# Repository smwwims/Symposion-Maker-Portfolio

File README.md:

# Symposion – Autonomous Service Robot (Maker Portfolio Version)

This repository is a public showcase of my **Symposion** transport robot project, created originally as my final mechatronics graduation project on top of a Festo Robotino platform. The private project repo (in German) also contained invoices and personal data, so this version focuses on the technical artefacts: **application code, mechanical CAD, and PCB design files**. It contains the **current implementation**, not the full incremental history.

## Software Overview

The main control programs for the robot are written in Festo’s proprietary environment **RobotinoView**, which combines Sequential Function Chart (SFC) and Function Block Diagram (FBD) and allows integrating **Python scripts as custom function blocks**. RobotinoView provides blocks for each integrated hardware component, libraries for robotics functions such as odometry, and mathematical operations; the entire **autonomous driving and docking logic** is implemented in this environment.

Python scripts act as intermediaries between the web interface, custom sensors, and the Robotino framework. The following scripts are used as function blocks inside the main RobotinoView program:

- `alarm.py` – triggers sound and light signals in case of an impending collision.
- `encoder.py` – passes encoder measurements to the web interface.
- `readPath.py` – retrieves permanently stored routes from a CSV file.
- `restart.py` – sends a restart signal to Robotino once it has reached the last waypoint.

Because I added custom sensors (ToF distance sensors, IR receiver/transmitter) and outputs (LED strips) that cannot be connected directly to Robotino’s I/O, I integrated an **Arduino Nano as an intermediate controller**.

- `k3_control.ino` runs continuously on the Nano, reading ToF distance values and IR receiver signals and outputting color commands as PWM signals to the LED strips.
- In parallel, `k3_communication.py` runs on Robotino’s Ubuntu-based control unit (started automatically via `startSymposion.sh`). It establishes a USB connection to the Arduino, writes distance measurements into `.txt` files that RobotinoView reads, and forwards color commands from the Flask web interface to the Arduino.

The **web interface** is built with the Flask framework. It can either talk to Robotino hardware via a REST API or write control data into `.txt` files that are consumed by the other software modules.

## Repository Structure

### `Software/`

Contains the Python scripts, Arduino code, and supporting files used alongside RobotinoView. RobotinoView project files themselves are not easily diff‑friendly, but the structure and naming of the Python and Arduino modules mirror the logical modules described in the project documentation (route following, docking, safety, communication).

### `Mechanics/`

Contains the **mechanical design files** for the robot add‑ons I designed. This includes:

- The **linear axis** mounted on top of the Robotino for the height‑adjustable platform.
- The **circular platform table** with carved bottle placements.
- The **internal platform** for additional sensors and electronics.
- Exported formats suitable for viewing (e.g., STEP) and integration into other CAD assemblies.

Vendor parts such as the Robotino base, standard aluminum profiles, and hardware are represented using manufacturer CAD where available.

### `Electronics/`

Contains the **PCB design artefacts** and related documentation for the custom Arduino peripheral interface board (“K3 – Arduino Peripheral IF”). This includes:

- **Schematics**
- **Board Layouts**
- **Bill of Materials (BoM)** with reference designators, descriptions, and supplier part numbers for key components (MOSFETs, connectors, resistors, capacitors, and the PCB itself).

This board interfaces 5 V sensors (ToF, IR receiver), drives LED strips, and communicates with Robotino’s control unit via USB through an Arduino Nano.

## Notes

- This repo is intended as a **readable technical snapshot** of the project, not as a polished, general‑purpose library.
- For a complete system description (mechanics, electronics, software, risk analysis, and operating manual), see the accompanying [project documentation](Symposion_SMW_2023_EN.pdf).

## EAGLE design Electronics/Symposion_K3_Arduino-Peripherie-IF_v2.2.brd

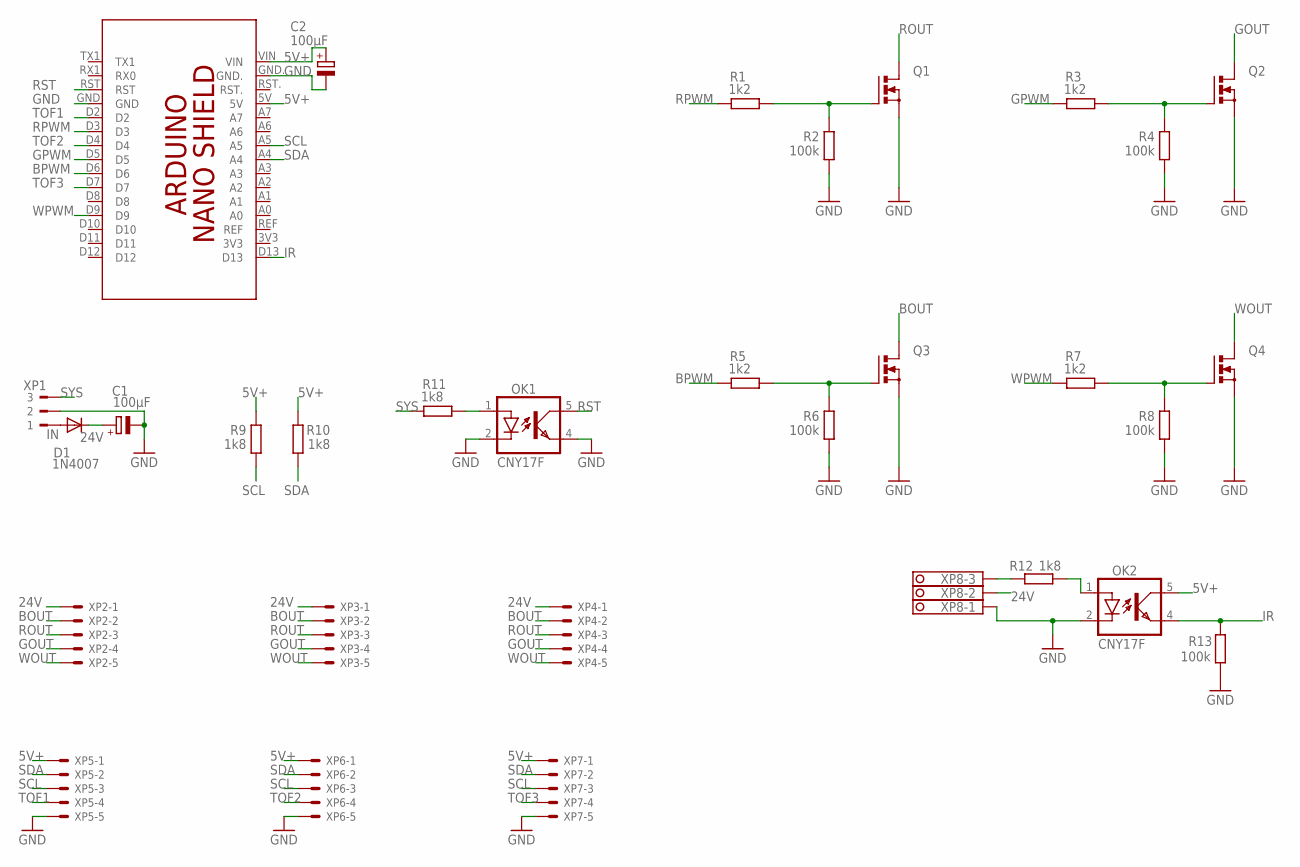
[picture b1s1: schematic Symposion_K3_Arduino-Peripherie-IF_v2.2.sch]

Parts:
C1, C2: 100µF; RCL_E5-6
D1: 1N4007; DIODE_F126-10
OK1, OK2: CNY17F; DIL06
PCB1: 0_WSH_FAVORITES_ARDUINO_NANO
Q1, Q2, Q3, Q4: 0_WSH_FAVORITES_BUZ11BV; 0_WSH_FAVORITES_TO220BV
R1, R3, R5, R7: 1k2; R1206
R2, R4, R6, R8, R13: 100k; R1206
R9, R10, R11, R12: 1k8; R1206
XP1: 180-3
XP2, XP3, XP4, XP5, XP6, XP7: 22-27-2051-05; 6410-05
XP8: 1751251

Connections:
5V+: C2.+, OK2.5 (COL), PCB1.5V, PCB1.VIN, R9.1, R10.1, XP5.1, XP6.1, XP7.1
24V: C1.+, D1.C, XP2.1, XP3.1, XP4.1, XP8.2
BOUT: Q3.D, XP2.2, XP3.2, XP4.2
BPWM: PCB1.D6, R5.2
GND: C1.-, C2.-, OK1.2 (C), OK1.4 (EMIT), OK2.2 (C), PCB1.GND, PCB1.GND., Q1.S, Q2.S, Q3.S, Q4.S, R2.2, R4.2, R6.2, R8.2, R13.2, XP1.2, XP5.5, XP6.5, XP7.5, XP8.1
GOUT: Q2.D, XP2.4, XP3.4, XP4.4
GPWM: PCB1.D5, R3.2
IN: D1.A, XP1.1
IR: OK2.4 (EMIT), PCB1.D13, R13.1
unnamed: Q1.G, R1.1, R2.1
unnamed: OK1.1 (A), R11.1
unnamed: Q2.G, R3.1, R4.1
unnamed: Q3.G, R5.1, R6.1
unnamed: OK2.1 (A), R12.1
unnamed: Q4.G, R7.1, R8.1
unnamed: R12.2, XP8.3
ROUT: Q1.D, XP2.3, XP3.3, XP4.3
RPWM: PCB1.D3, R1.2
RST: OK1.5 (COL), PCB1.RST
SCL: PCB1.A5, R9.2, XP5.3, XP6.3, XP7.3
SDA: PCB1.A4, R10.2, XP5.2, XP6.2, XP7.2
SYS: R11.2, XP1.3
TOF1: PCB1.D2, XP5.4
TOF2: PCB1.D4, XP6.4
TOF3: PCB1.D7, XP7.4
WOUT: Q4.D, XP2.5, XP3.5, XP4.5
WPWM: PCB1.D9, R7.2

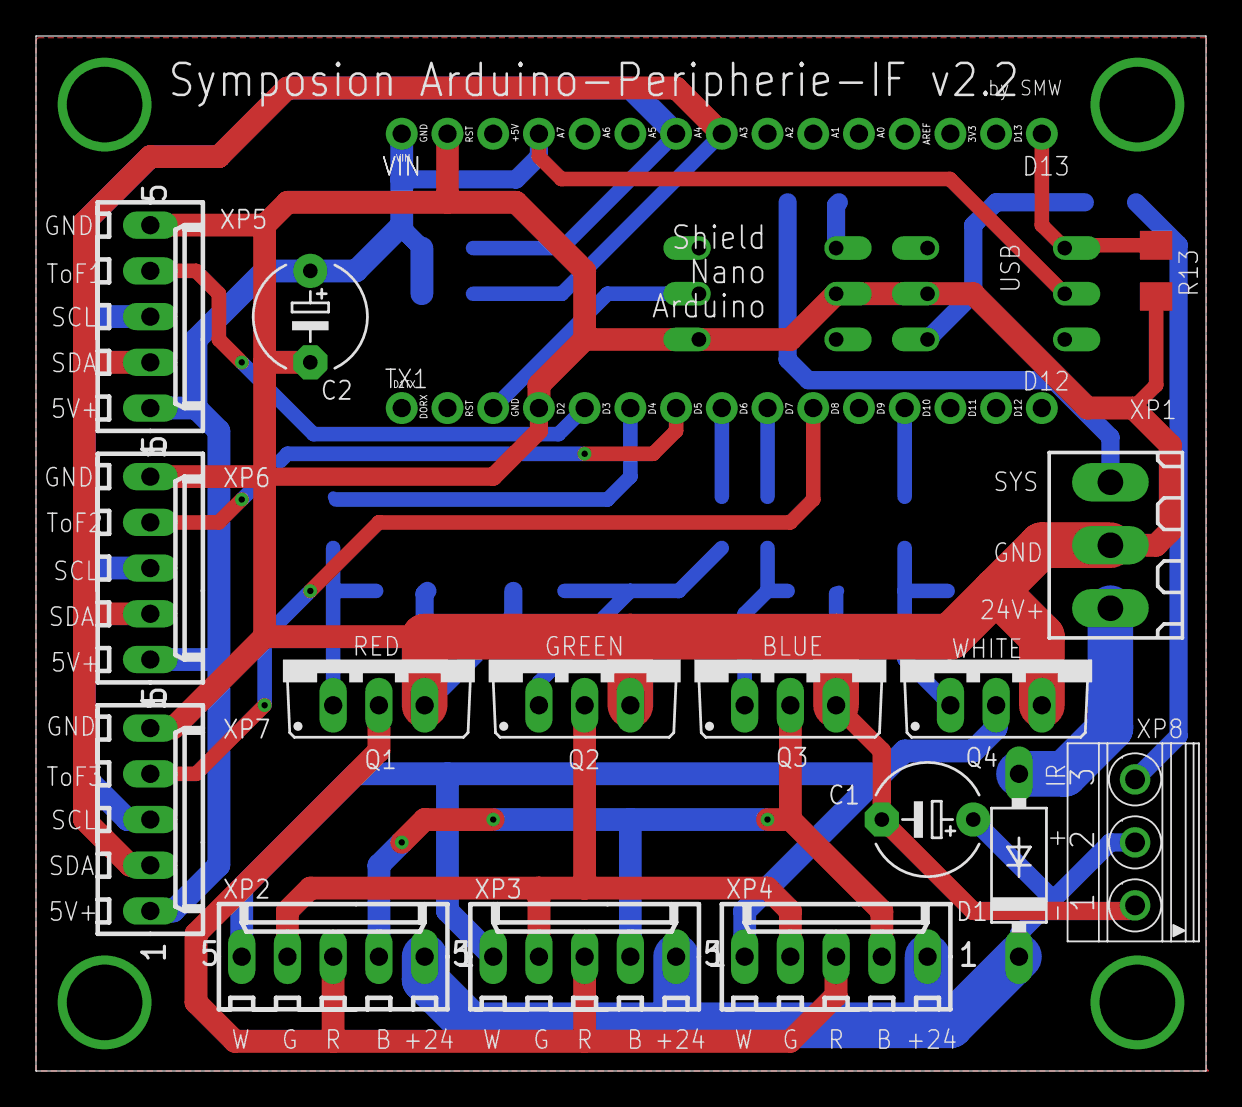
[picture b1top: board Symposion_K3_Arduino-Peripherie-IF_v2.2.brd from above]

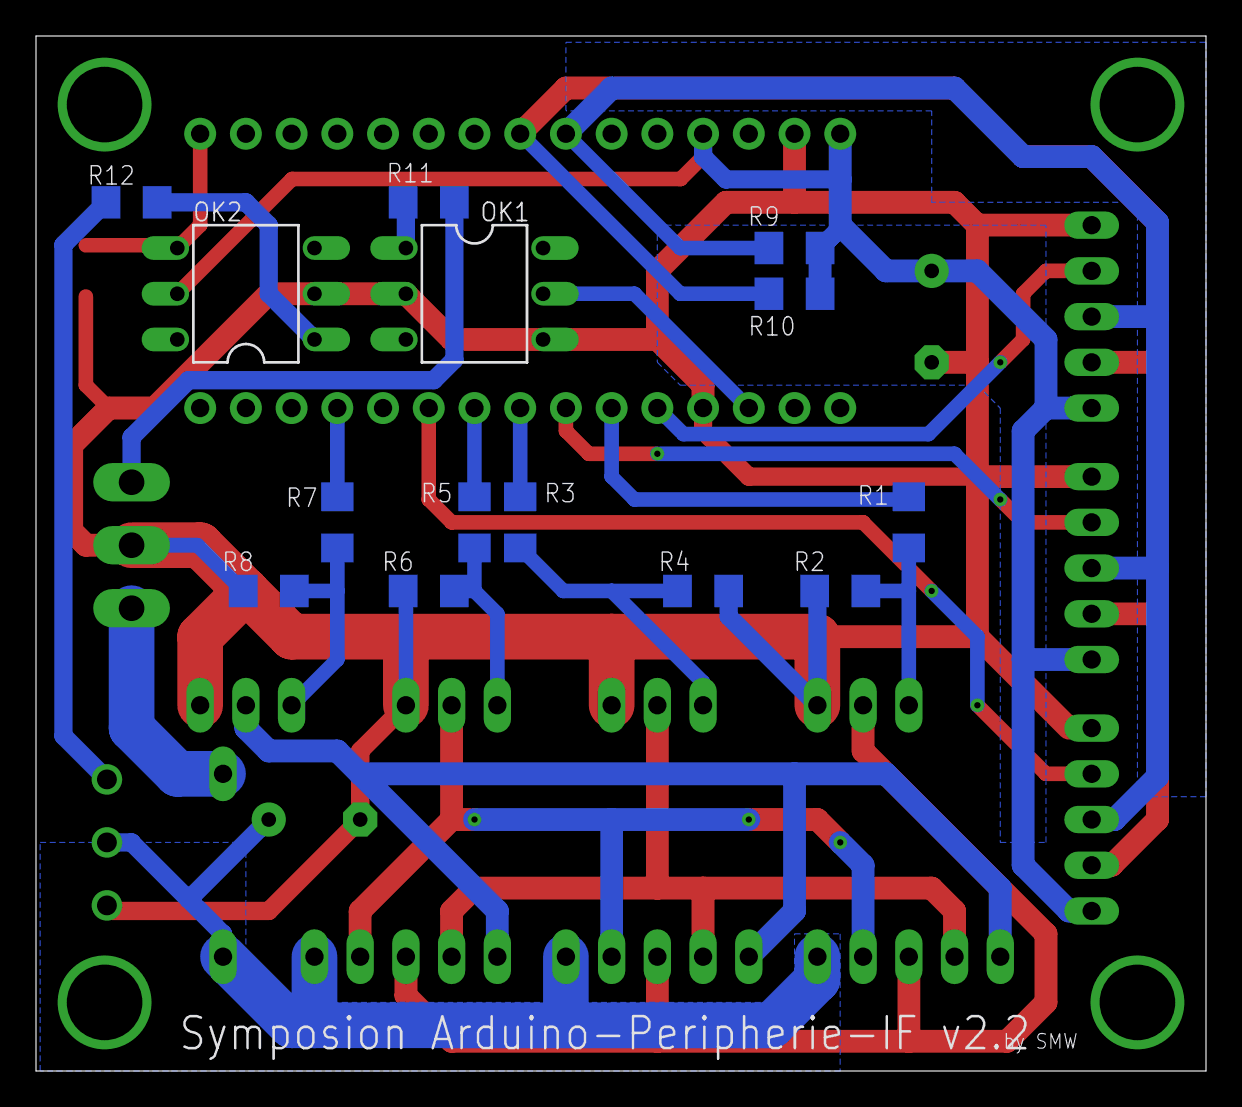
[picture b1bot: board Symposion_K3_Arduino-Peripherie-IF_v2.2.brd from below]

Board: 2 copper layers, 65.0 x 57.5 mm, 31 parts (14 on the bottom side), 27 nets.

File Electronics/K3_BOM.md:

# K3 – Arduino Peripheral Interface Board  
Bill of Materials

| Qty | Unit | Reference        | Description                          | Additional details                              | Value / Part number      | Supplier            | Order no.           |
|-----|------|------------------|--------------------------------------|------------------------------------------------|--------------------------|---------------------|---------------------|
| 1   | pcs  | D1               | Universal diode                      | 1000 V, 1 A                                     | 1N4007                   | RS Components       | 917-5386           |
| 6   | pcs  | XP2–XP7          | Pin header, Molex                    | Straight, 5‑pin, single row, 2.54 mm pitch      | 22-27-2051               | RS Components       | 170-7104           |
| 1   | pcs  | OK1              | Optocoupler                          | 6‑pin, phototransistor output                   | CNY17F                   | RS Components       | 178-0898           |
| 2   | pcs  | PCB1             | Socket strip                         | 20‑pin, single row, 2.54 mm pitch, straight     | SPL 20                   | Reichelt Elektronik | SPL 20             |
| 4   | pcs  | Q1–Q4            | N‑channel MOSFET                     | TO‑220AB, 50 V, 35 A                            | BUZ 11                   | Reichelt Elektronik | BUZ 11             |
| 4   | pcs  | R1, R3, R5, R7   | SMD chip resistor                    | 1206 package, 1% tolerance                      | 1.2 kΩ                   | RS Components       | 223-2271           |
| 4   | pcs  | R2, R4, R6, R8   | SMD chip resistor                    | 1206 package, 1% tolerance                      | 100 kΩ                   | RS Components       | 223-2524           |
| 3   | pcs  | R9, R10, R11     | SMD chip resistor                    | 1206 package, 1% tolerance                      | 1.8 kΩ                   | RS Components       | 223-2293           |
| 1   | pcs  | XP1              | Terminal header                      | 3‑pin, 3.5 mm pitch, 90°                        | 180-3                    | Reichelt Elektronik | CTB932HD-3         |
| 1   | pcs  | XP1 (plug)       | Pluggable screw terminal             | 3‑pin, 3.5 mm pitch, 0°                         | 180-3                    | Reichelt Elektronik | CTB922HD-3         |
| 2   | pcs  | C1, C2           | Aluminum electrolytic capacitor      | Radial, 5 mm lead spacing, 35 V                 | 100 µF                   | Farnell             | 2466947            |
| 1   | pcs  | K3               | PCB                                  | 2‑layer, 1.6 mm, HASL finish                    | “Beautiful Board Simple” | Aisler              | UMCVKSHQ – Rev. 6  |

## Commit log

2025-12-17 Add pcb files
2025-12-17 Add drawings
2025-12-17 Add 3d files
2025-12-17 Add codebase
2025-12-17 Add project dossier
2025-12-18 Add project documentation link in README
2025-12-18 Add project pictures
2025-12-18 Add demo video of autonomous driving mode
2025-12-18 Add demo video of docking
